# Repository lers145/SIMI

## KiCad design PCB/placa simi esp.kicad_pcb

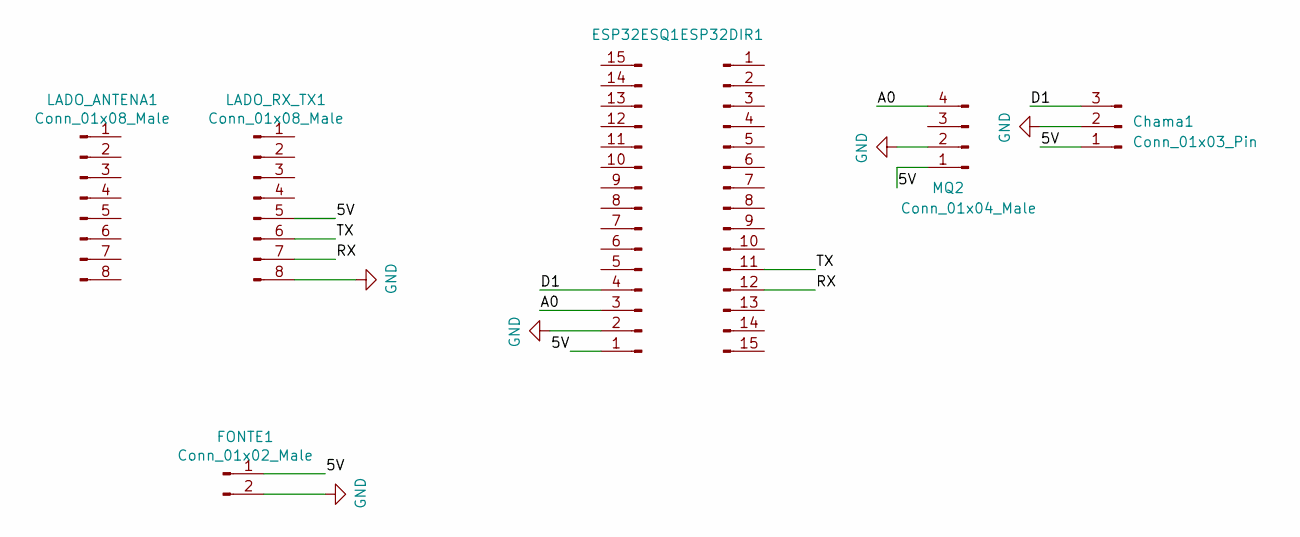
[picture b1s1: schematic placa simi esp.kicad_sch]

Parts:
Chama1: Conn_01x03_Pin; PinSocket_1x03_P2.54mm_Vertical
ESP32DIR1, ESP32ESQ1: Conn_01x15_Pin; PinSocket_1x15_P2.54mm_Vertical
FONTE1: Conn_01x02_Male; TerminalBlock_bornier-2_P5.08mm
LADO_ANTENA1: Conn_01x08_Male; PinSocket_1x08_P2.54mm_Vertical
LADO_RX_TX1: Conn_01x08_Male; PinSocket_1x08_P2.54mm_Vertical
MQ2: Conn_01x04_Male; PinSocket_1x04_P2.54mm_Vertical

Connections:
/5V: Chama1.1, ESP32ESQ1.1, FONTE1.1, LADO_RX_TX1.5, MQ2.1
/A0: ESP32ESQ1.3, MQ2.4
/D1: Chama1.3, ESP32ESQ1.4
/RX: ESP32DIR1.12, LADO_RX_TX1.7
/TX: ESP32DIR1.11, LADO_RX_TX1.6
GND: Chama1.2, ESP32ESQ1.2, FONTE1.2, LADO_RX_TX1.8, MQ2.2

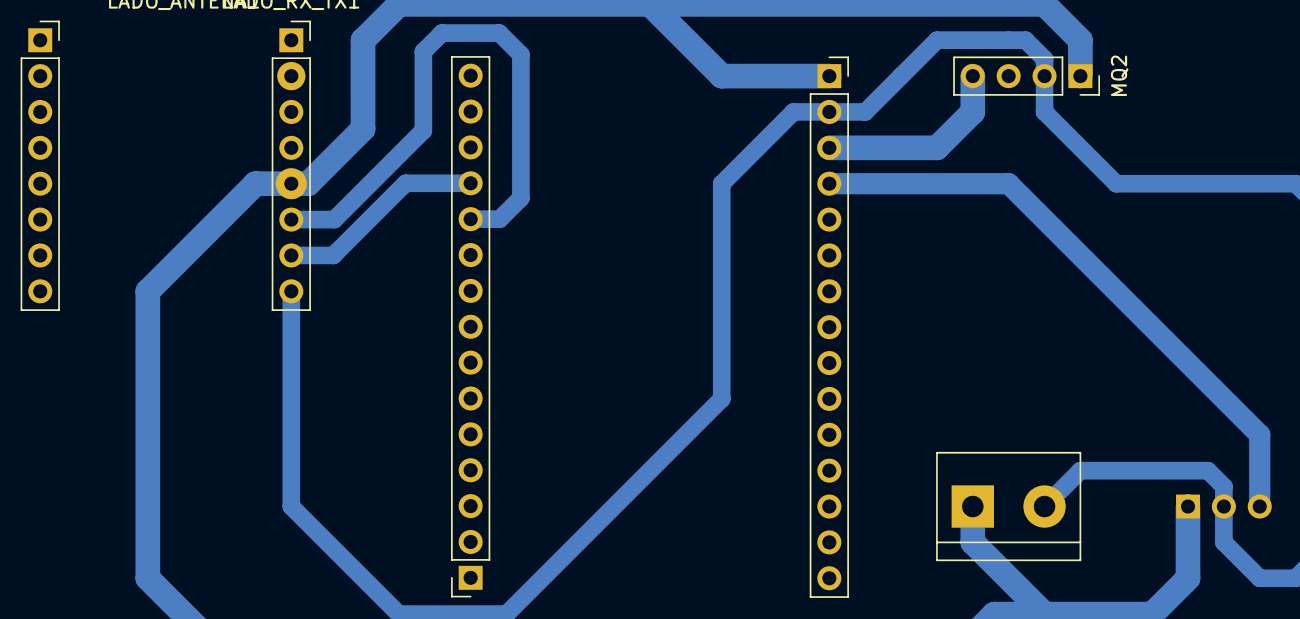
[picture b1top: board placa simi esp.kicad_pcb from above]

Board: 2 copper layers, 7 parts (1 on the bottom side), 6 nets.
